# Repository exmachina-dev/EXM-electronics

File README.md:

```
____ _  _ _  _    ____ _    ____ ____ ___ ____ ____ _  _ _ ____ ____ 
|___  \/  |\/| __ |___ |    |___ |     |  |__/ |  | |\ | | |    [__  
|___ _/\_ |  |    |___ |___ |___ |___  |  |  \ |__| | \| | |___ ___] 
                                                                      
```

# EXM electronics

This repo contains all necessary files to design and produce PCBs for the ExMachina product range.

## File format and folder structure

Documentation files should be in PDF. Board image files can be in PNG or PDF.

PCB design files are in EAGLE Standard edition (7.4) file format.

The following are general rules to help maintain a consistent folder structure:

* All libraries are placed inside the shared libraries repository. It can be found
  on [Github](https://github.com/exmchina-dev/eagle-resources)

* One board for each project folder.  

* Mutiples revisions can be placed inside a subfolder. i.e. `SwitchEthernet/Rev A1`

* BOMs, partlists, spreadsheet and Gerber should placed inside a `MDP/` folder.  

## STATUS
|		Board		|	Rev  |		|
|-------------------|--------|------|
|DMX Proto			| Rev A1 | :ok: |
|Emergency Stop 	| Rev A3 | :ok: |
|EXM Encoder 		| Rev A1 | :ok: |
|EXM HMI LED 		| Rev A1 | :ok: |
|EXM Relay Four		| Rev A1 | :ok: |
|EXM Relay One		| Rev A3 | :ok: |
|EXM Relay Three	| Rev A2 | :ok: |
|Switch Ethernet 	| Rev A5 | :ok: |

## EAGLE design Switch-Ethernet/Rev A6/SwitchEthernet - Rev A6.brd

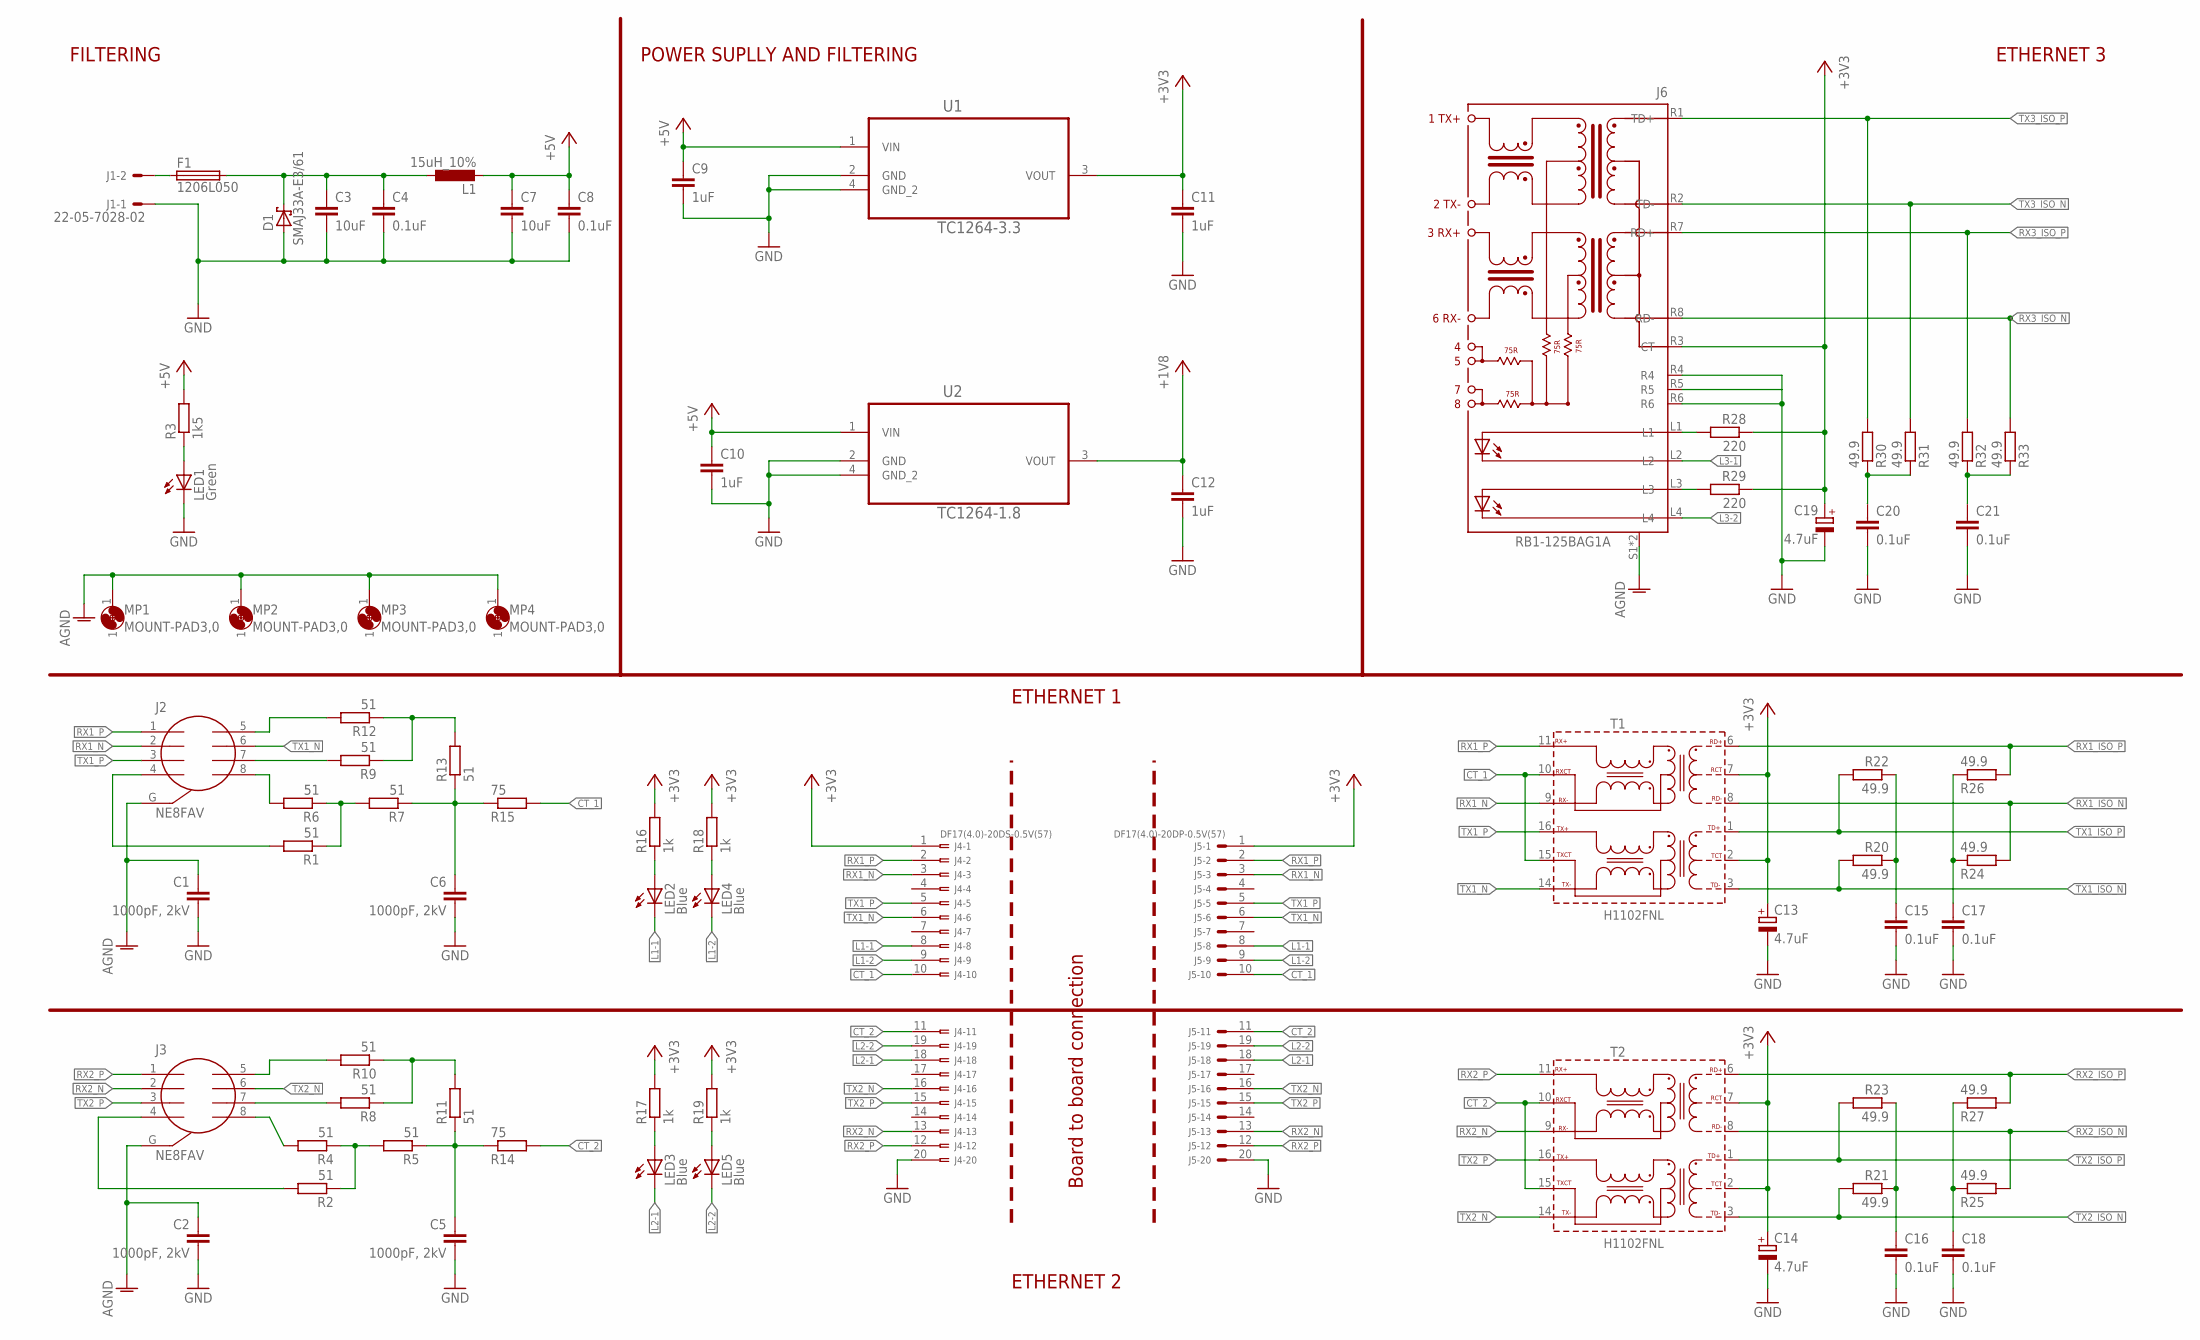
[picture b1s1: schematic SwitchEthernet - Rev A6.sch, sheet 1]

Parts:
C1, C2, C5, C6: 1000pF, 2kV; C1206; MPN MC1206B102K202CT
C3, C7: 10uF; C0603; MPN GRM32DR71C106KA01L
C4, C8, C15, C16, C17, C18, C20, C21: 0.1uF; C0603; MPN GRM188R71H104KA93D
C9, C10, C11, C12: 1uF; C0603; MPN GRM188R61C105KA93D
C13, C14, C19: 4.7uF; CT3216; MPN T491A475K016AT
D1: SMAJ33A-E3/61; DIODE_DO-214AC; MPN SMAJ33A-E3/61
F1: 1206L050; 1206L; MPN 1206L050YR
J1: 22-05-7028-02; 7395-02; MPN 22-05-7028
J2, J3: NE8FAV
J4: DF17(4.0)-20DS-0.5V(57); DF17-20DS; MPN DF17(4.0)-20DS-0.5V(57)
J5: DF17(4.0)-20DP-0.5V(57); DF17-20DP; MPN DF17(4.0)-20DP-0.5V(57)
J6: RB1-125BAG1A; WIZNET_RB1-125BAG1A
L1: 15uH_10%; L4532M; MPN LQH43CN150K03L
LED1: Green; CHIP-LED0603; MPN OVS-0604
LED2, LED3, LED4, LED5: Blue; CHIP-LED0603; MPN OVS-0603
MP1, MP2, MP3, MP4: MOUNT-PAD3,0; P3,0
R1, R2, R4, R5, R6, R7, R8, R9, R10, R11, R12, R13: 51; R0603; MPN RC0603FR-0751RL
R3: 1k5; R0603; MPN RC0603FR-071K5L
R14, R15: 75; R0603; MPN RC0603FR-0775RL
R16, R17, R18, R19: 1k; R0603; MPN RC0603FR-071KL.
R20, R21, R22, R23, R24, R25, R26, R27, R30, R31, R32, R33: 49.9; R0603; MPN MCWR06X49R9FTL
R28, R29: 220; R0603; MPN RC0603FR-07220RL
T1, T2: H1102FNL; HXXXX
U1: TC1264-3.3; SOT230P700X180-4N
U2: TC1264-1.8; SOT230P700X180-4N

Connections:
+1V8: C12.1, U2.3 (VOUT); also elsewhere on the board
+3V3: C11.1, C13.+, C14.+, C19.+, J4.1, J5.1, J6.R3 (CT), R16.2, R17.2, R18.2, R19.2, R28.1, R29.1, T1.2 (TCT), T1.7 (RCT), T2.2 (TCT), T2.7 (RCT), U1.3 (VOUT); also elsewhere on the board
+5V: C7.1, C8.1, C9.1, C10.1, L1.2, R3.2, U1.1 (VIN), U2.1 (VIN)
AGND: C1.1, C2.1, J2.G, J3.G, J6.S1, J6.S2, MP1.1, MP2.1, MP3.1, MP4.1
CT_1: J4.10, J5.10, R15.2, T1.10 (RXCT), T1.15 (TXCT)
CT_2: J4.11, J5.11, R14.2, T2.10 (RXCT), T2.15 (TXCT)
GND: C1.2, C2.2, C3.2, C4.2, C5.2, C6.2, C7.2, C8.2, C9.2, C10.2, C11.2, C12.2, C13.-, C14.-, C15.2, C16.2, C17.2, C18.2, C19.-, C20.2, C21.2, D1.2 (A), J1.1, J4.20, J5.20, J6.R4, J6.R5, J6.R6, LED1.C, U1.2 (GND), U1.4 (GND_2), U2.2 (GND), U2.4 (GND_2); also elsewhere on the board
L1-1: J4.8, J5.8, LED2.C; also elsewhere on the board
L1-2: J4.9, J5.9, LED4.C; also elsewhere on the board
L2-1: J4.18, J5.18, LED3.C; also elsewhere on the board
L2-2: J4.19, J5.19, LED5.C; also elsewhere on the board
L3-1: J6.L2; also elsewhere on the board
L3-2: J6.L4; also elsewhere on the board
unnamed: F1.1, J1.2
unnamed: J3.8, R4.2
unnamed: J2.4, R1.2
unnamed: J2.8, R6.2
unnamed: J2.7, R9.2
unnamed: C15.1, R20.1, R22.1
unnamed: J2.5, R12.2
unnamed: J3.7, R8.2
unnamed: C5.1, R5.1, R11.1, R14.1
unnamed: R1.1, R6.1, R7.2
unnamed: J3.4, R2.2
unnamed: R2.1, R4.1, R5.2
unnamed: R9.1, R12.1, R13.2
unnamed: J3.5, R10.2
unnamed: R8.1, R10.1, R11.2
unnamed: LED2.A, R16.1
unnamed: LED1.A, R3.1
unnamed: C20.1, R30.1, R31.1
unnamed: LED4.A, R18.1
unnamed: LED3.A, R17.1
unnamed: LED5.A, R19.1
unnamed: C21.1, R32.1, R33.1
unnamed: C6.1, R7.1, R13.1, R15.1
unnamed: C17.1, R24.1, R26.1
unnamed: J6.L3, R29.2
unnamed: J6.L1, R28.2
unnamed: C16.1, R21.1, R23.1
unnamed: C18.1, R25.1, R27.1
PW: C3.1, C4.1, D1.1 (C), F1.2, L1.1
RX1_ISO_N: R24.2, T1.8 (RD-); also elsewhere on the board
RX1_ISO_P: R26.2, T1.6 (RD+); also elsewhere on the board
RX1_N: J2.2, J4.3, J5.3, T1.9 (RX-)
RX1_P: J2.1, J4.2, J5.2, T1.11 (RX+)
RX2_ISO_N: R25.2, T2.8 (RD-); also elsewhere on the board
RX2_ISO_P: R27.2, T2.6 (RD+); also elsewhere on the board
RX2_N: J3.2, J4.13, J5.13, T2.9 (RX-)
RX2_P: J3.1, J4.12, J5.12, T2.11 (RX+)
RX3_ISO_N: J6.R8 (RD-), R33.2; also elsewhere on the board
RX3_ISO_P: J6.R7 (RD+), R32.2; also elsewhere on the board
TX1_ISO_N: R20.2, T1.3 (TD-); also elsewhere on the board
TX1_ISO_P: R22.2, T1.1 (TD+); also elsewhere on the board
TX1_N: J2.6, J4.6, J5.6, T1.14 (TX-)
TX1_P: J2.3, J4.5, J5.5, T1.16 (TX+)
TX2_ISO_N: R21.2, T2.3 (TD-); also elsewhere on the board
TX2_ISO_P: R23.2, T2.1 (TD+); also elsewhere on the board
TX2_N: J3.6, J4.16, J5.16, T2.14 (TX-)
TX2_P: J3.3, J4.15, J5.15, T2.16 (TX+)
TX3_ISO_N: J6.R2 (TD-), R31.2; also elsewhere on the board
TX3_ISO_P: J6.R1 (TD+), R30.2; also elsewhere on the board

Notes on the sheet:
FILTERING
POWER SUPLLY AND FILTERING
ETHERNET 3
ETHERNET 1
ETHERNET 2
Board to board connection

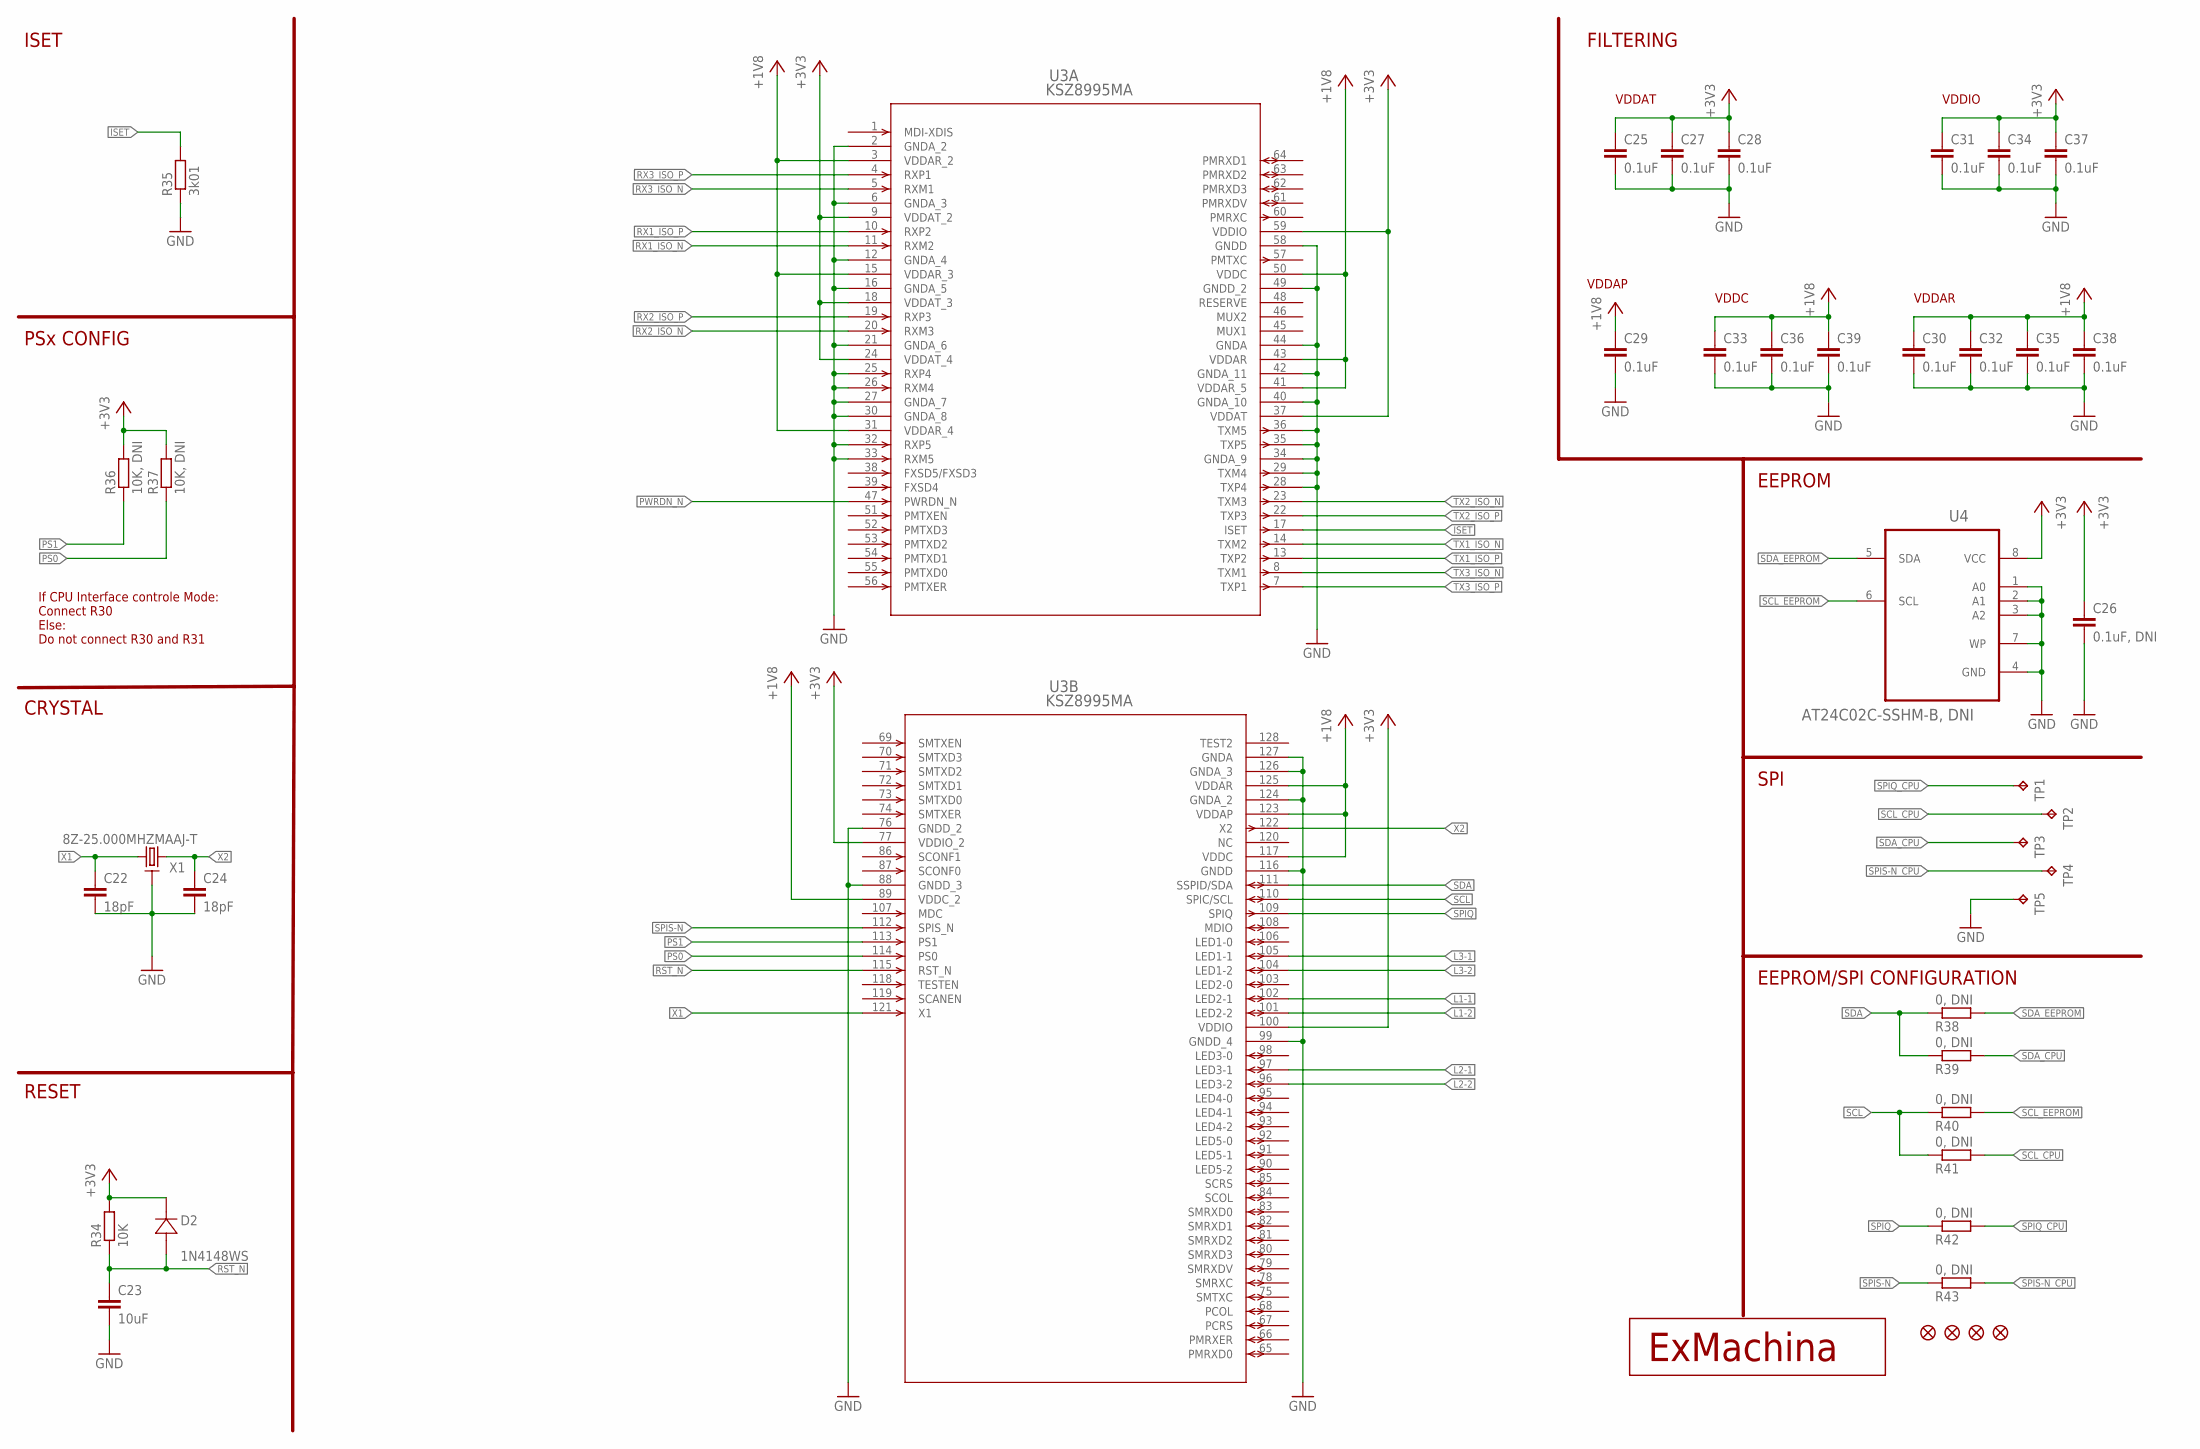
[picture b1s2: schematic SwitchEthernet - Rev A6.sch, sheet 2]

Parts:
C22, C24: 18pF; C0603; MPN GRM1885C1H180JA01D
C23: 10uF; C0603; MPN GRM32DR71C106KA01L
C25, C27, C28, C29, C30, C31, C32, C33, C34, C35, C36, C37, C38, C39: 0.1uF; C0603; MPN GRM188R71H104KA93D
C26: 0.1uF, DNI; C0603; MPN GRM188R71H104KA93D
D2: 1N4148WS; SOD323-W; MPN 1N4148WS
JP1, JP2, JP3, JP4: FIDUCIAL1X2; FIDUCIAL-1X2
R34: 10K; R0603; MPN RC0603FR-0710KL
R35: 3k01; R0603; MPN MCMR06X3001FTL
R36, R37: 10K, DNI; R0603; MPN RC0603FR-0710KL
R38, R39, R40, R41, R42, R43: 0, DNI; R0603; MPN RC0603FR-070RL
T3: EXMACHINA-LOGO-NAME; EXM-LOGO-BASELINE
TP1, TP2, TP3, TP4, TP5: TPB1,27; B1,27
U3: KSZ8995MA; PQFP-128_MQL; MPN KSZ8995MA
U4: AT24C02C-SSHM-B, DNI; SOIC127P600X175-8N
X1: 8Z-25.000MHZMAAJ-T; SMD2.5X2; MPN 8Z-25.000MAAJ-T

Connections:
+1V8: C29.1, C30.1, C32.1, C33.1, C35.1, C36.1, C38.1, C39.1, U3.3 (VDDAR_2), U3.15 (VDDAR_3), U3.31 (VDDAR_4), U3.41 (VDDAR_5), U3.43 (VDDAR), U3.50 (VDDC), U3.89 (VDDC_2), U3.117 (VDDC), U3.123 (VDDAP), U3.125 (VDDAR); also elsewhere on the board
+3V3: C25.1, C26.1, C27.1, C28.1, C31.1, C34.1, C37.1, D2.C (1), R34.2, R36.2, R37.2, U3.9 (VDDAT_2), U3.18 (VDDAT_3), U3.24 (VDDAT_4), U3.37 (VDDAT), U3.59 (VDDIO), U3.77 (VDDIO_2), U3.100 (VDDIO), U4.8 (VCC); also elsewhere on the board
GND: C22.2, C23.2, C24.2, C25.2, C26.2, C27.2, C28.2, C29.2, C30.2, C31.2, C32.2, C33.2, C34.2, C35.2, C36.2, C37.2, C38.2, C39.2, R35.1, TP5.TP, U3.2 (GNDA_2), U3.6 (GNDA_3), U3.12 (GNDA_4), U3.16 (GNDA_5), U3.21 (GNDA_6), U3.25 (RXP4), U3.26 (RXM4), U3.27 (GNDA_7), U3.28 (TXP4), U3.29 (TXM4), U3.30 (GNDA_8), U3.32 (RXP5), U3.33 (RXM5), U3.34 (GNDA_9), U3.35 (TXP5), U3.36 (TXM5), U3.40 (GNDA_10), U3.42 (GNDA_11), U3.44 (GNDA), U3.49 (GNDD_2), U3.58 (GNDD), U3.76 (GNDD_2), U3.88 (GNDD_3), U3.99 (GNDD_4), U3.116 (GNDD), U3.124 (GNDA_2), U3.126 (GNDA_3), U3.127 (GNDA), U4.1 (A0), U4.2 (A1), U4.3 (A2), U4.4 (GND), U4.7 (WP), X1.2, X1.4 (2); also elsewhere on the board
ISET: R35.2, U3.17 (ISET)
L1-1: U3.102 (LED2-1); also elsewhere on the board
L1-2: U3.101 (LED2-2); also elsewhere on the board
L2-1: U3.97 (LED3-1); also elsewhere on the board
L2-2: U3.96 (LED3-2); also elsewhere on the board
L3-1: U3.105 (LED1-1); also elsewhere on the board
L3-2: U3.104 (LED1-2); also elsewhere on the board
PS0: R37.1, U3.114 (PS0)
PS1: R36.1, U3.113 (PS1)
PWRDN_N: U3.47 (PWRDN_N)
RST_N: C23.1, D2.A (2), R34.1, U3.115 (RST_N)
RX1_ISO_N: U3.11 (RXM2); also elsewhere on the board
RX1_ISO_P: U3.10 (RXP2); also elsewhere on the board
RX2_ISO_N: U3.20 (RXM3); also elsewhere on the board
RX2_ISO_P: U3.19 (RXP3); also elsewhere on the board
RX3_ISO_N: U3.5 (RXM1); also elsewhere on the board
RX3_ISO_P: U3.4 (RXP1); also elsewhere on the board
SCL: R40.1, R41.1, U3.110 (SPIC/SCL)
SCL_CPU: R41.2, TP2.TP
SCL_EEPROM: R40.2, U4.6 (SCL)
SDA: R38.1, R39.1, U3.111 (SSPID/SDA)
SDA_CPU: R39.2, TP3.TP
SDA_EEPROM: R38.2, U4.5 (SDA)
SPIQ: R42.1, U3.109 (SPIQ)
SPIQ_CPU: R42.2, TP1.TP
SPIS-N: R43.1, U3.112 (SPIS_N)
SPIS-N_CPU: R43.2, TP4.TP
TX1_ISO_N: U3.14 (TXM2); also elsewhere on the board
TX1_ISO_P: U3.13 (TXP2); also elsewhere on the board
TX2_ISO_N: U3.23 (TXM3); also elsewhere on the board
TX2_ISO_P: U3.22 (TXP3); also elsewhere on the board
TX3_ISO_N: U3.8 (TXM1); also elsewhere on the board
TX3_ISO_P: U3.7 (TXP1); also elsewhere on the board
X1: C22.1, U3.121 (X1), X1.1
X2: C24.1, U3.122 (X2), X1.3

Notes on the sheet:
ISET
FILTERING
VDDIO
VDDAT
VDDAR
VDDC
VDDAP
PSx CONFIG
If CPU Interface controle Mode: Connect R30 Else: Do not connect R30 and R31
CRYSTAL
EEPROM
SPI
EEPROM/SPI CONFIGURATION
RESET

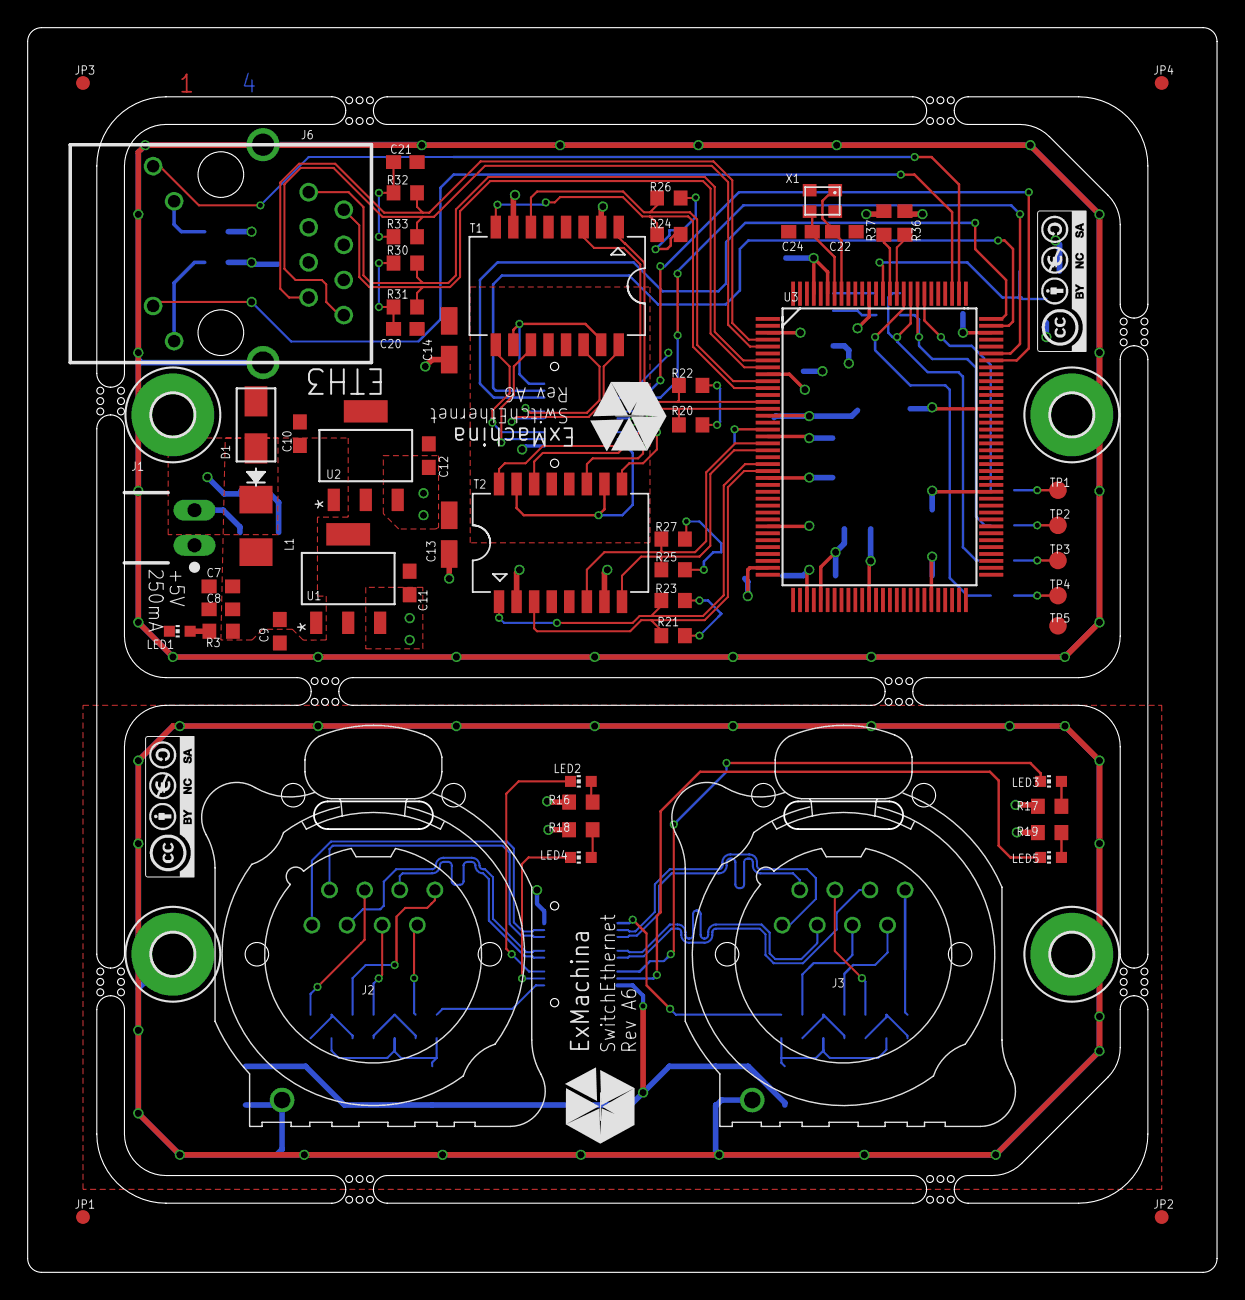
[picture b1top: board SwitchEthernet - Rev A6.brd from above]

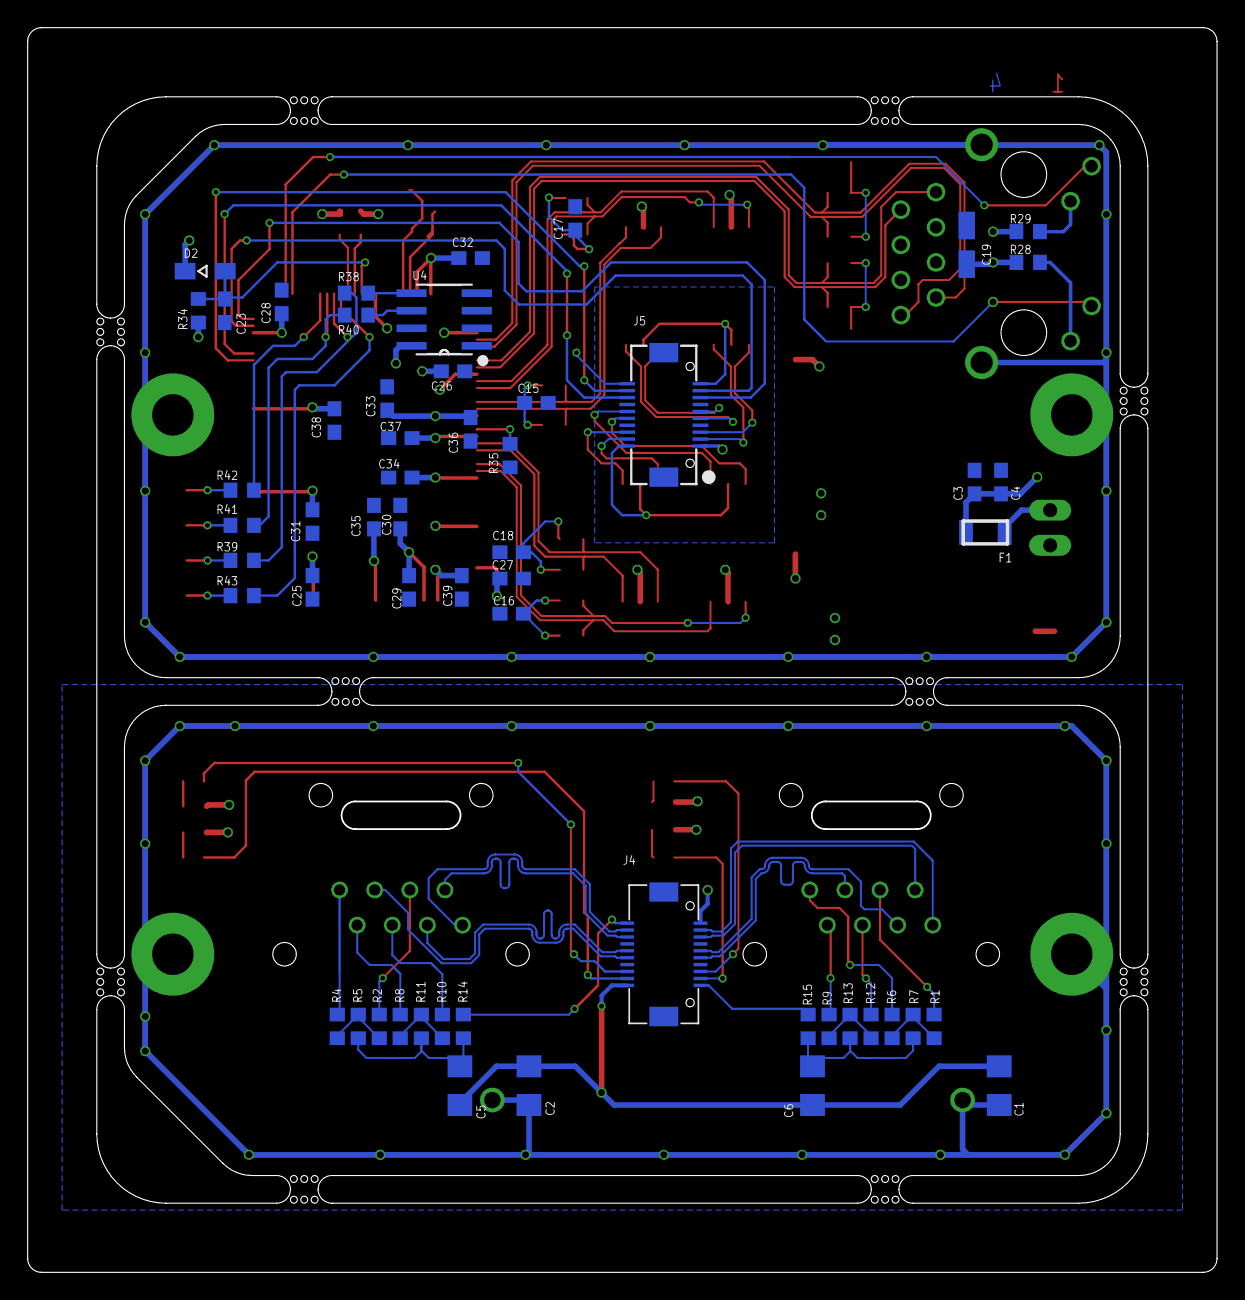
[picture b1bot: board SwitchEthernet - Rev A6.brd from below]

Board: 4 copper layers, 85.9 x 89.9 mm, 122 parts (56 on the bottom side), 78 nets.

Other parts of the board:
U$2, U$3: CC-BY-NC-SA
U$4: EXMACHINA-LOGO-NAME; EXM-LOGO-BASELINE
U$5: A5L-LOC

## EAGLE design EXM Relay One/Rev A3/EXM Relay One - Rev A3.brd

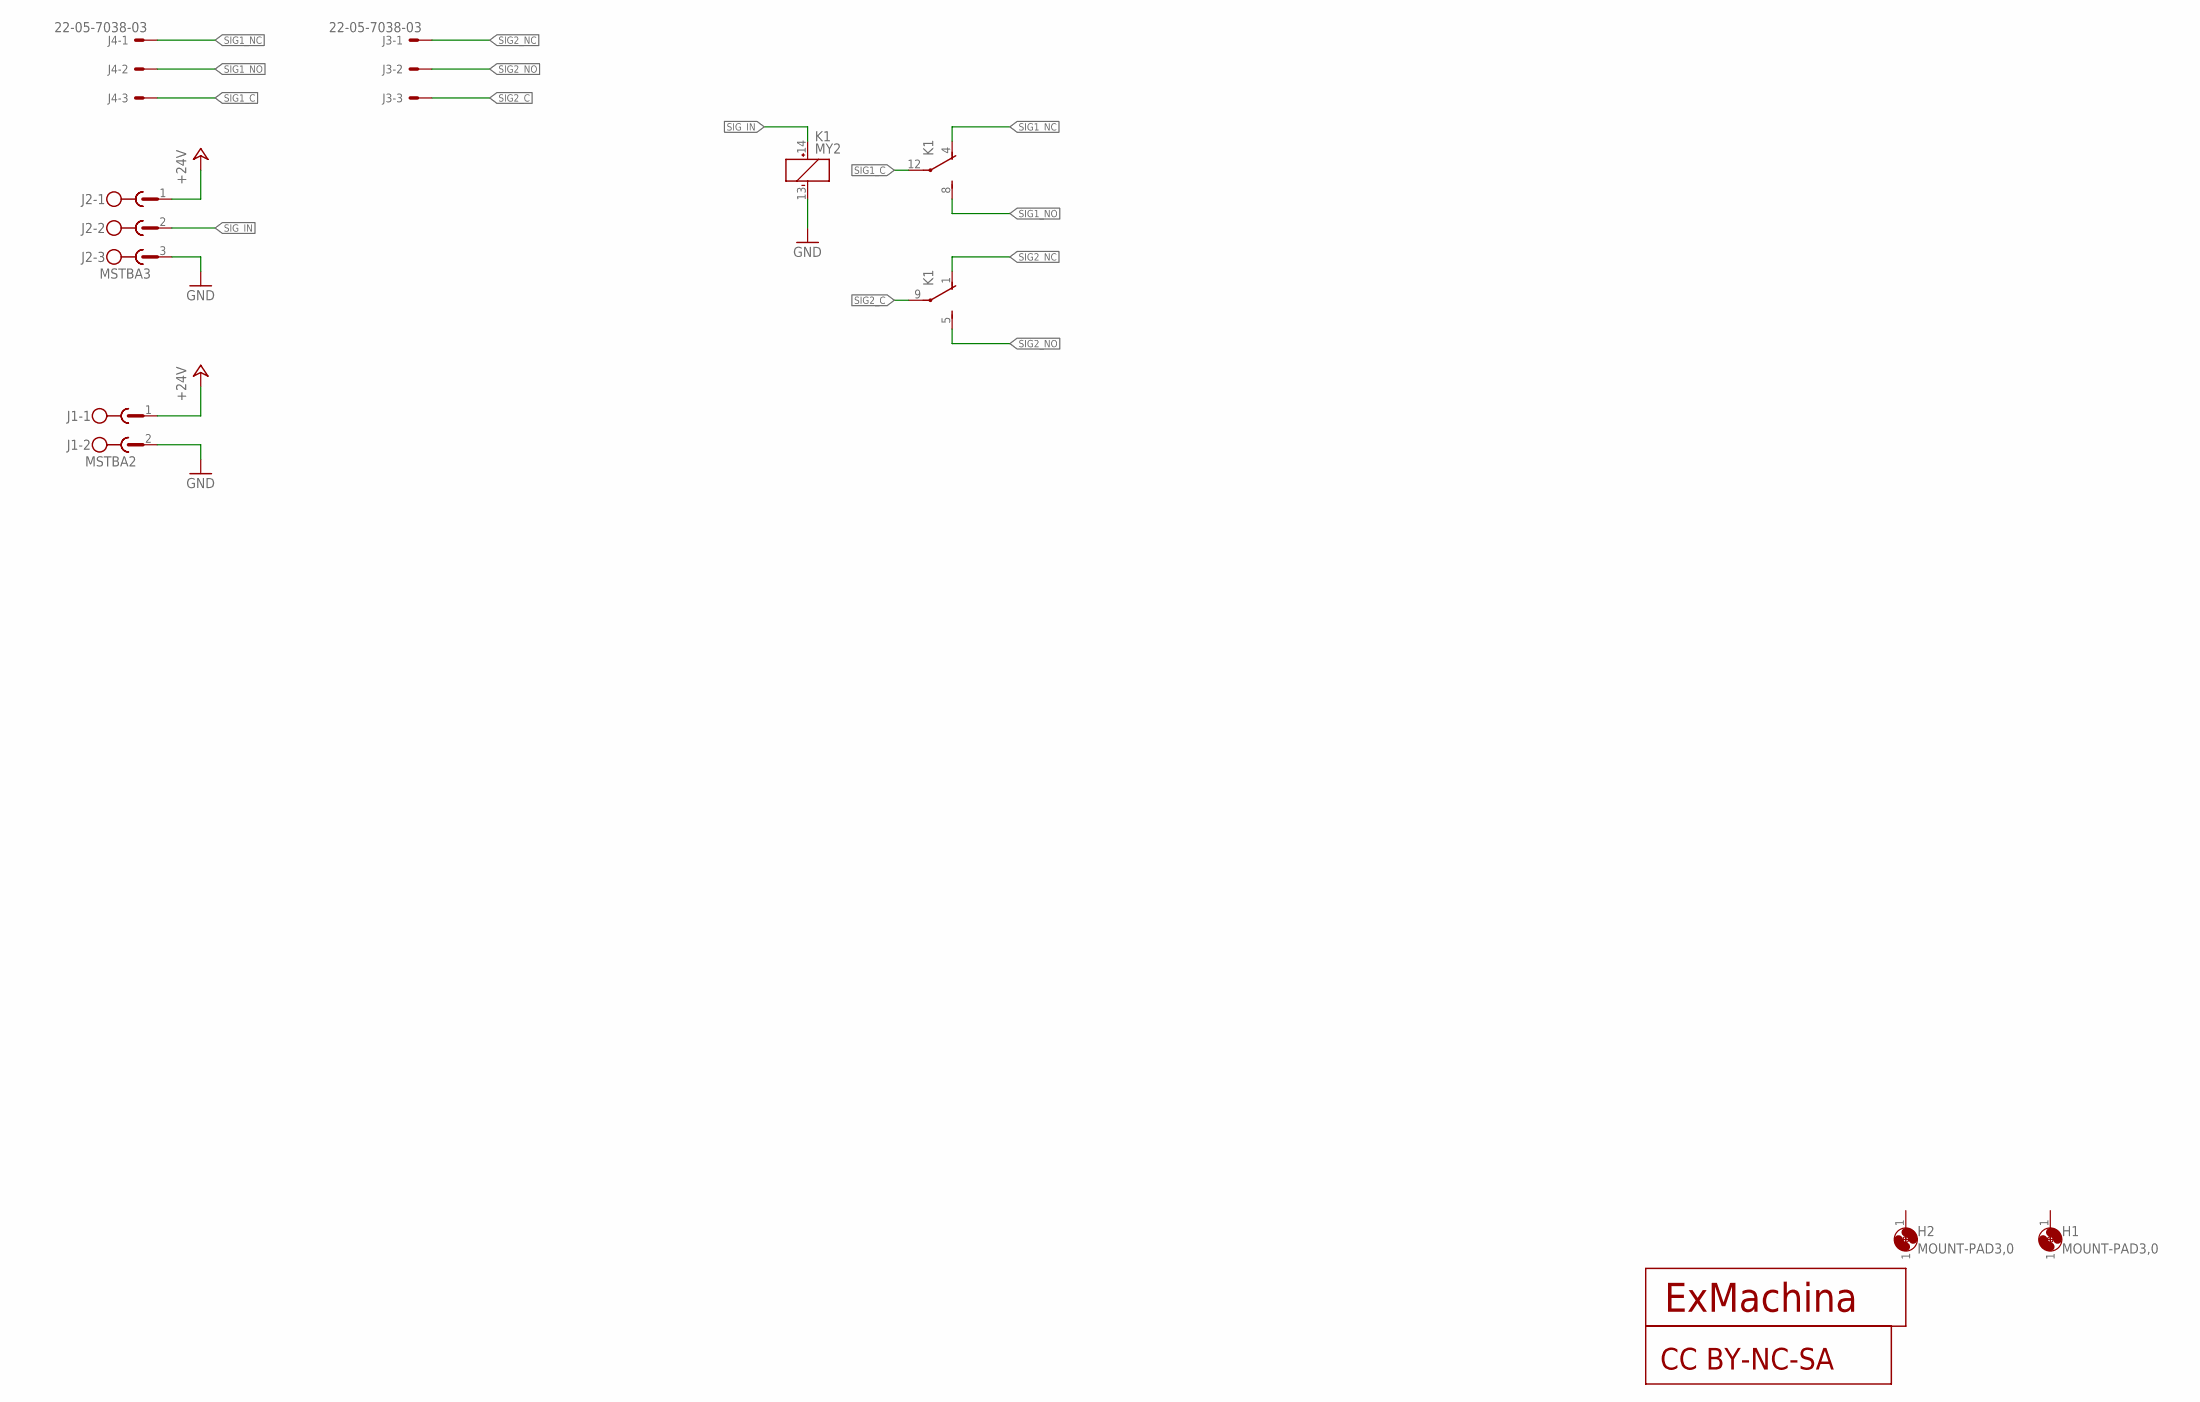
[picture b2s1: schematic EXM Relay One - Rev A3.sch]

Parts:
CC1: CC-BY-NC-SA
H1, H2: MOUNT-PAD3,0; P3,0
J1: MSTBA2
J2: MSTBA3
J3, J4: 22-05-7038-03; 7395-03
K1: MY2; PY08
T1: EXMACHINA-LOGO-NAME; EXM-LOGO-BASELINE

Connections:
+24V: J1.1, J2.1
GND: J1.2, J2.3, K1.13 (-)
SIG1_C: J4.3, K1.12 (C)
SIG1_NC: J4.1, K1.4 (NC)
SIG1_NO: J4.2, K1.8 (NO)
SIG2_C: J3.3, K1.9 (C)
SIG2_NC: J3.1, K1.1 (NC)
SIG2_NO: J3.2, K1.5 (NO)
SIG_IN: J2.2, K1.14 (+)

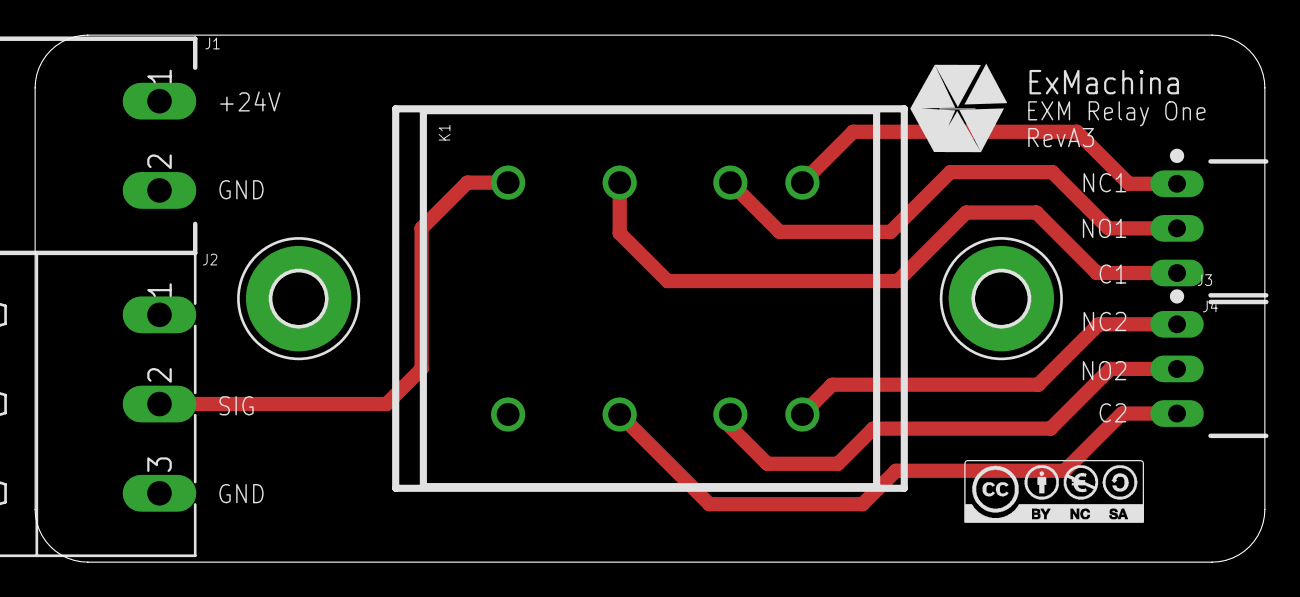
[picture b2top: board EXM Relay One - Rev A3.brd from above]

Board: 2 copper layers, 70.0 x 30.0 mm, 10 parts (0 on the bottom side), 9 nets.

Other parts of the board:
U$1: A4L-LOC

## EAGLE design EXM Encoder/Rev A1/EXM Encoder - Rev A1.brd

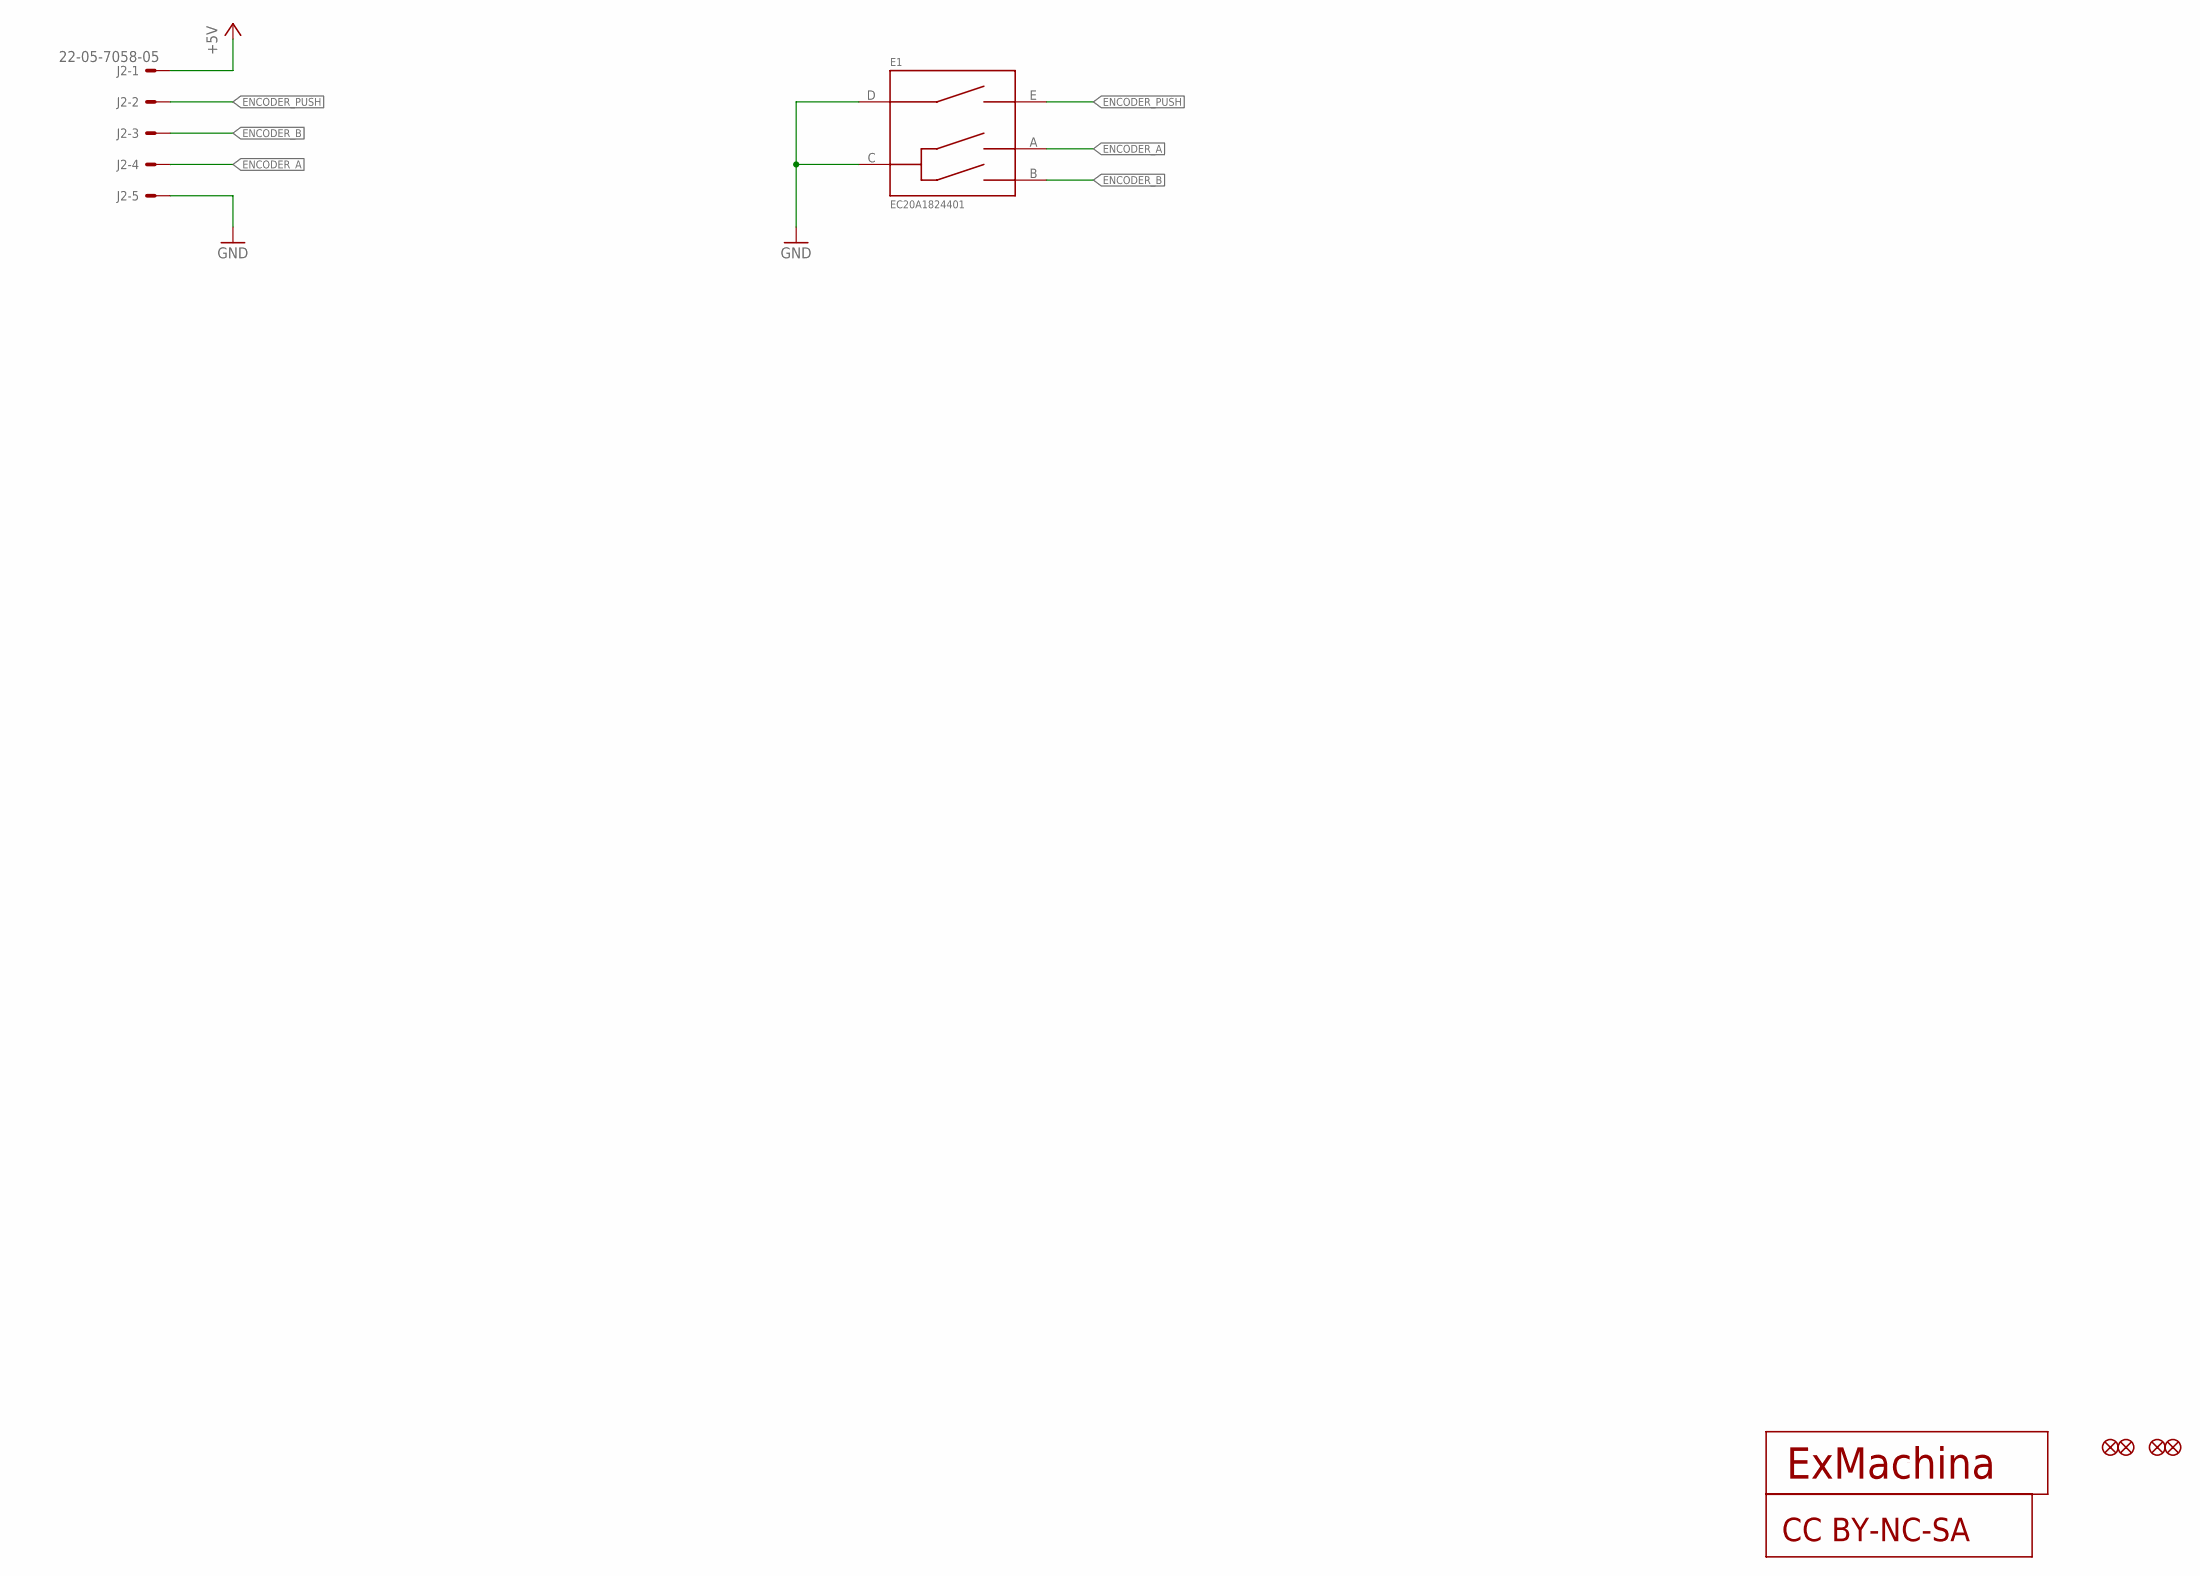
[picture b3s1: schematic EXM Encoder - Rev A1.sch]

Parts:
CC1: CC-BY-NC-SA
E1: EC20A1824401; EC20A
J2: 22-05-7058-05; 7395-05
JP1, JP2, JP3, JP4: FIDUCIAL1X2; FIDUCIAL-1X2
T1: EXMACHINA-LOGO-NAME; EXM-LOGO-BASELINE

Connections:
+5V: J2.1
ENCODER_A: E1.A (ENCODER_A), J2.4
ENCODER_B: E1.B (ENCODER_B), J2.3
ENCODER_PUSH: E1.E (PUSH), J2.2
GND: E1.C (COM), E1.D (COM_PUSH), J2.5

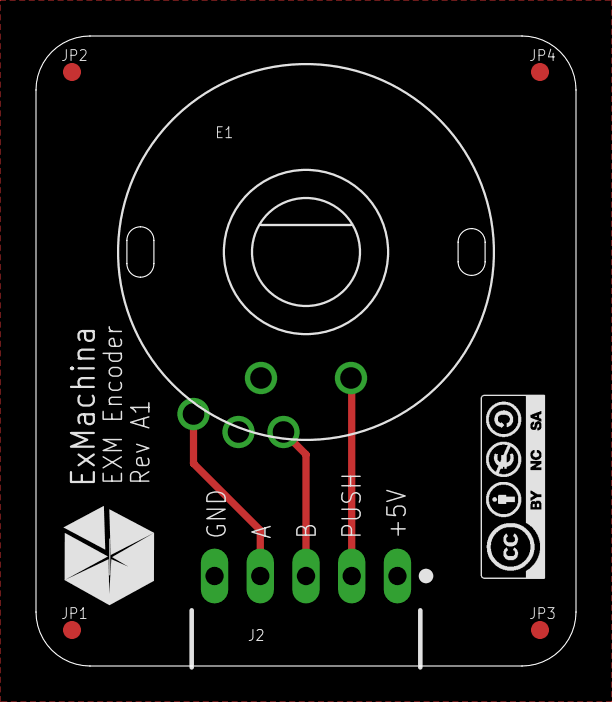
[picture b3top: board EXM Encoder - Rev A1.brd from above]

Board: 2 copper layers, 30.0 x 35.0 mm, 8 parts (0 on the bottom side), 4 nets.
